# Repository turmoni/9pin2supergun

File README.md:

# 9pin2supergun
A project to read a CD32, Mega Drive/Genesis, or generic 9-pin gamepad and output each control to a separate pin for use with Neo Geos and/or Superguns.

I am personally using this code with a [Monster Joysticks CD32 joystick](https://monsterjoysticks.com/deluxe-cd32-retro-joystick-kit-classic) and a [Minigun Supergun](https://www.arcade-projects.com/threads/minigun-supergun-an-open-source-supergun.9408/).

There is a chance that there will be USB host support in the future, if using [the PCB](pcb/).

## Hardware

There are two expected paths to getting the hardware needed to use this; either build the PCB, or hook up a Pi Pico. For the most compact setup, but needing some more moderate to advanced soldering skills, build the PCB. For a potentially easier build, hook up a Pi Pico.

The PCB's files and some basic instructions can be found in [the pcb directory](pcb/). This isn't for people who are new to soldering - it has surface mount components, a dense layout, and the RP2040 package is very fine pitched.

Schematics and a reference PCB for hooking up a Pi Pico, along with details about the parts used, can be found in [the pico_reference directory](pico_reference/).

## Installation

If you don't want to customise anything, grab the latest uf2 file from [the releases page](https://github.com/turmoni/9pin2supergun/releases/) that matches your setup and install it to your board by holding down BOOTSEL when plugging it in to a PC, and then copying the file on to the storage device that appears. The PCB's BOOTSEL button is at the top-right. The options are:

* 9pin2supergun-**pcb**-v\*.uf2 - if you're using [the PCB I designed](pcb/)
* 9pin2supergun-**pico**-v\*.uf2 - if you're wiring up a Pico as per the schematic

Don't worry if you're missing optional components, the code shouldn't care.

## Usage

Once you've got a board programmed, using it is pretty much a case of setting the switch to the right position, plugging it in, and going! If you've fitted the LED, it will tell you which mode you're in:
* Red: Amiga CD32 mode
* Blue: Mega Drive/generic mode
* Yellow: Mega Drive/generic mode with the buttons swapped

The button mapping is as follows:

| Output | CD32[^1]  | Mega Drive/Genesis (6- or 3-button) | Generic 9-pin |
| ------ | --------  | ----------------------------------- | ------------- |
| Up     | Up        | Up                                  | Up            |
| Down   | Down      | Down                                | Down          |
| Left   | Left      | Left                                | Left          |
| Right  | Right     | Right                               | Right         |
| 1      | G         | A                                   | 1             |
| 2      | Y         | B                                   | 2             |
| 3      | LS        | C                                   | N/A           |
| 4      | R         | X                                   | N/A           |
| 5      | B         | Y                                   | N/A           |
| 6      | RS        | Z                                   | N/A           |
| Start  | Pause     | Start                               | 1 + 2         |
| Coin   | Pause + G | Mode                                | N/A           |

Of course, X, Y, Z, and Mode aren't present on a 3-button Mega Drive controller, so these buttons aren't available there.

Since the Mega Drive layout may be the opposite of what's wanted, you can press and hold mode for three seconds to swap ABC and XYZ.

If you don't want the 1+2 mapping for generic 9-pin controllers, set `MAP_GENERIC_AB_TO_START` to false and rebuild the code. If you don't want the Pause + Green mapping for CD32 controllers, or want it to be a different button combination, change `CD32_COIN_BITMASK` (there are comments in the code to explain its format). Since these are pretty niche, I'm not sure figuring out a runtime configuration option is worth it.

## Building the code

This project is based on the [rp2040 project template](https://github.com/rp-rs/rp2040-project-template), have a look there for details. You need a `rust` build environment and the project will build with Cargo.

If you're using a Pi Pico, rather than the PCB, pass the `--features pi_pico` flag to `cargo` when building to get the right pin assignments.

## Anything else

This polls at 125Hz for the CD32 - I don't know whether a real CD32 pad will be happy with this, but I don't see why it wouldn't. The timing for each polling burst is based on what I observed with my PAL Amiga 500+, so that should be fine, but it was only polling at 50Hz. Given how little time is spent polling compared to waiting even at 125Hz, though, I can't imagine what issues might arise.

The Mega Drive controller support polls at around 140Hz.

Current draw seems fairly low, hovering at around 20-25mA on the controllers I've tested it with. If you're worried, power it up via USB (not whilst connected to a 15-pin port!) and use a USB power meter to see how much it's drawing.

## Credits

Thanks to [Mathew Carr's PSCD32 Development Diary](https://www.mrdictionary.net/PSCD32/diary/2019_08_09.htm) for documenting how the CD32 protocol actually works, and to [the RetroSix Wiki's Mega Drive controller page](https://www.retrosix.wiki/controller-interface-sega-mega-drive) for documenting the Mega Drive bits.

[^1]: Single-letter CD32 buttons refer to the colour, LB and RB are the shoulder buttons

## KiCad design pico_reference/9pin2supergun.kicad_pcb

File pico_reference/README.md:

# 9pin2supergun Reference Pico Design

This is a KiCad project for hooking up a Pi Pico to the appropriate hardware to get a fully working setup. As I see it, there are three main purposes for this project:

* To provide the schematic to use if wiring one up by hand, e.g. on a breadboard
* To give me PCBs based on the schematic so I can test that the schematic I've provided actually works, and is what the code expects
* To give a foundation for making new PCBs with different hardware than what I happened to have on hand

# Using the schematic

The schematic is hopefully fairly simple to understand, and can be found either by opening this project up in KiCad, or by looking at [the rendered PDF](rendered/sch.pdf).

# Building a PCB

First up: you probably don't want to use the PCB I've designed. The layout was literally done in about 20 minutes, with very little care given to routing traces to be neat, and it's designed to use the hardware I had on hand. If you want to use the components I've specified, I recommend instead using [the main PCB](../pcb), which is more compact and not *that* much harder to solder than what I have here.

If you do want to modify it, the KiCad project is in this directory.

For convenience each push gets rendered to [the `rendered` directory](rendered/) as a PDF of the schematics, a set of gerber files, and a BOM as a CSV, but again, you probably don't want to use the generated fabrication files as-is.

# Components and their explanations

If you're going to use your own components, the key things are:
 * U2 ([SN74LVC8T245](https://www.ti.com/product/SN74LVC8T245)) - this is just level shifting the input from the controller down to 3.3V. If you want to try out the Pico's 5V tolerance, you can omit this and RN1 if you want. Often the inputs will be either floating or GND, and so safe anyway, but I wouldn't totally rely on this being the case
 * U3/U4 ([SN74LVC2T45DCUR](https://www.ti.com/product/SN74LVC2T45)) - two-bit level shifters. U3 handles those that are always outputs, and U4 handles pin 6, which can either be an input or an output.
 * RN1 (10k resistor network) - pulling up the inputs from the controller port. Omit it if you're also omitting the level shifters
 * SW1 (SPDT switch) - the mode switch. Switches between Mega Drive (floating) and CD32 (tied to GND) modes. You can hardcode this if you're only using one type of controller
 * SW2 (standard push button) - not actually used, but might be helpful in the future
 * D1 (WS2812B LED) - indicates what mode you're in (including if the button rows are flipped in Mega Drive mode). Omit this if you don't care.

## More on level shifting

To recap, the level shifter U2 handles those inputs that are only ever inputs (pulled up to 5V). U3 handles both of the two outputs that can also be the +5V supply. U4 handles the one remaining pin that's either an input or an output depending on whether it's in CD32 or Mega Drive mode. There is nothing particularly special about any of these, they're just directional level shifters that can handle translating 3.3V to 5V or vice versa.
 
The connections to the DE9 connector are as follows:

| Pin | CD32 Function | CD32 Direction | Mega Drive Function | MD Direction |
| --- | ------------- | -------------- | ------------------- | ------------ |
| 1   | Up            | In             | Up/Z                | In           |
| 2   | Down          | In             | Down/Y              | In           |
| 3   | Left          | In             | Left/X/GND          | In           |
| 4   | Right         | In             | Right/Mode/GND      | In           |
| 5   | Latch         | Out            | +5V                 | Out          |
| 6   | Fire 1/Clock  | Out            | B/A                 | In           |
| 7   | +5V           | Out            | Select              | Out          |
| 8   | GND           | N/A            | GND                 | N/A          |
| 9   | Fire 2/Data   | In             | C/Start             | In           |

As the table shows, the DE9 connector is a lot simpler if you're only targetting a single platform; for a CD32, you can permanently wire pin 7 to +5V, and pin 6 as an output, whereas with a Mega Drive controller you can wire pin 5 to +5V and pin 6 as an input. You may also be able to get away with not needing level shifters in this case, if you're willing to risk +5V into your Pico's GPIO pins, and your controller recognises 3.3V logic levels.

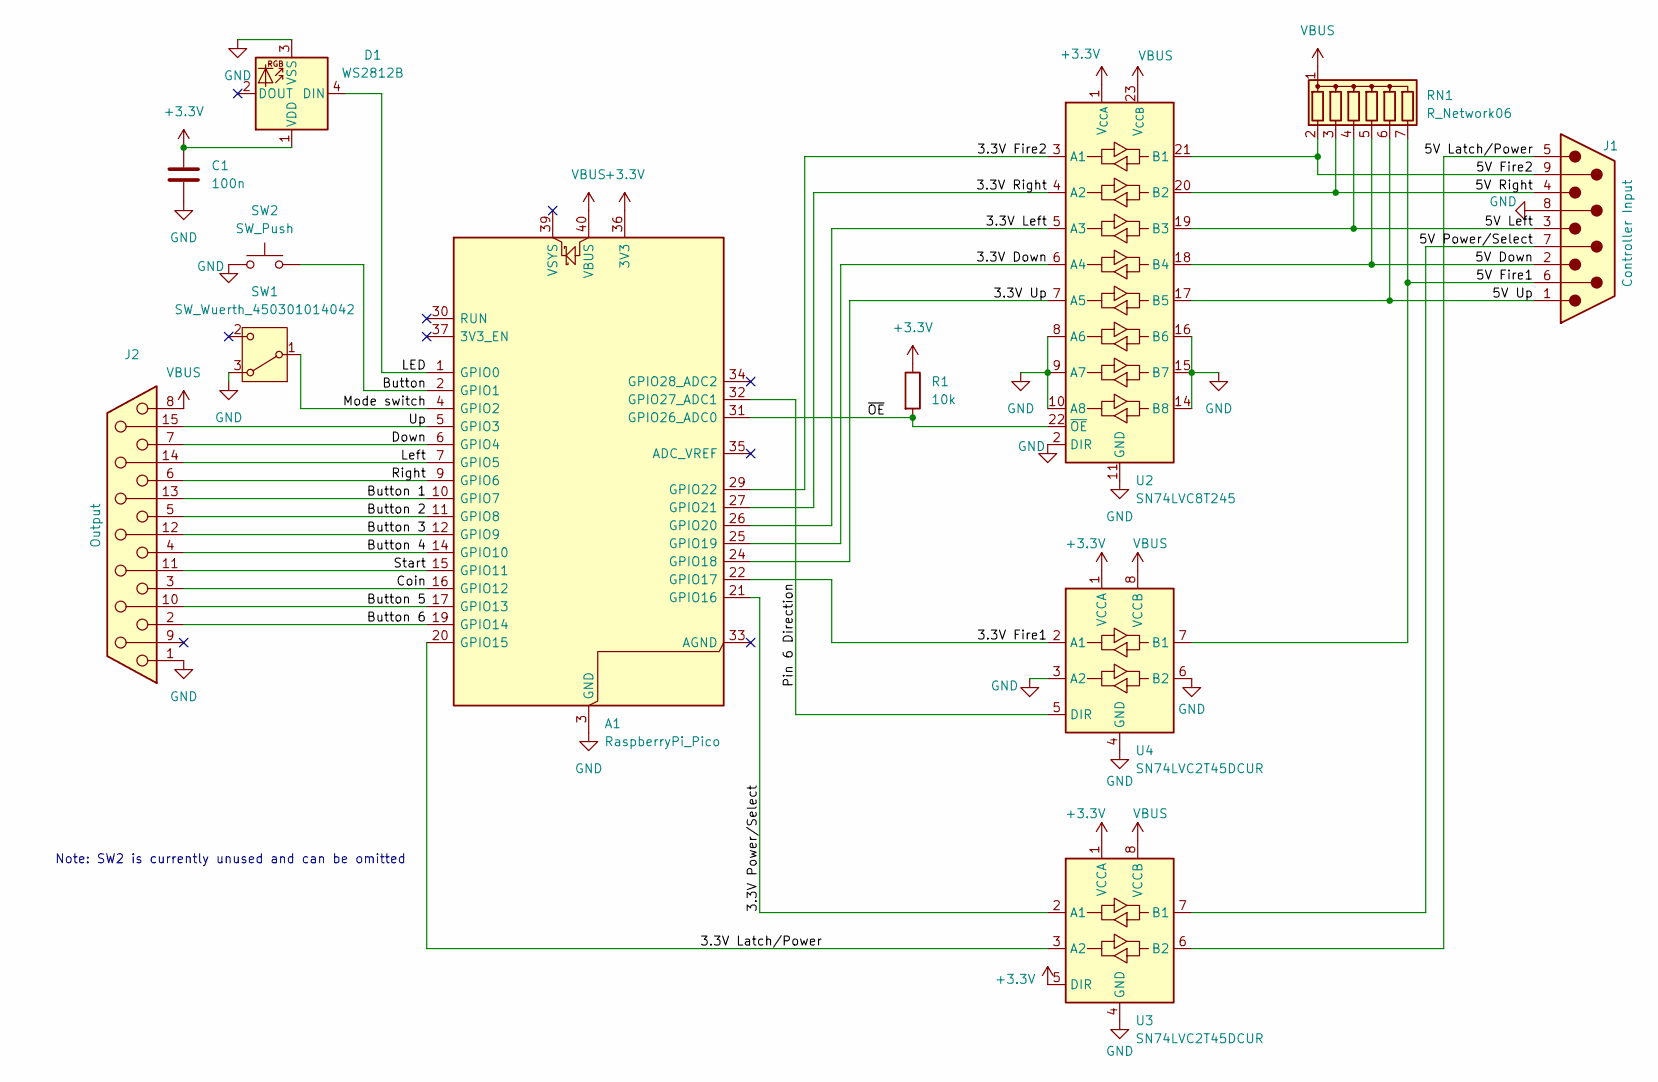
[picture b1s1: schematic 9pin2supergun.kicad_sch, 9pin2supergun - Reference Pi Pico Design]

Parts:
A1: RaspberryPi_Pico; RaspberryPi_Pico_Common_Unspecified
C1: 100n; C_Disc_D5.0mm_W2.5mm_P5.00mm
D1: WS2812B; LED_WS2812B_PLCC4_5.0x5.0mm_P3.2mm
J1: Controller Input; DSUB-9_Pins_Horizontal_P2.77x2.84mm_EdgePinOffset7.70mm_Hou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
J2: Output; DSUB-15_Socket_Horizontal_P2.77x2.84mm_EdgePinOffset7.70mm_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
R1: 10k; R_Axial_DIN0309_L9.0mm_D3.2mm_P12.70mm_Horizontal
RN1: R_Network06; R_Array_SIP7
SW1: SW_Wuerth_450301014042; SW_Slide-03_Wuerth-WS-SLTV_10x2.5x6.4_P2.54mm
SW2: SW_Push; SW_PUSH_6mm
U2: SN74LVC8T245; TSSOP-24_4.4x7.8mm_P0.65mm
U3, U4: SN74LVC2T45DCUR; VSSOP-8_2.3x2mm_P0.5mm

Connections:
+3.3V: A1.36 (3V3), C1.1, D1.1 (VDD), R1.1, U2.1 (V_{CCA}), U3.1 (VCCA), U3.5 (DIR), U4.1 (VCCA)
/3.3V Down: A1.25 (GPIO19), U2.6 (A4)
/3.3V Fire1: A1.22 (GPIO17), U4.2 (A1)
/3.3V Fire2: A1.29 (GPIO22), U2.3 (A1)
/3.3V Latch/Power: A1.20 (GPIO15), U3.3 (A2)
/3.3V Left: A1.26 (GPIO20), U2.5 (A3)
/3.3V Power/Select: A1.21 (GPIO16), U3.2 (A1)
/3.3V Right: A1.27 (GPIO21), U2.4 (A2)
/3.3V Up: A1.24 (GPIO18), U2.7 (A5)
/5V Down: J1.2, RN1.5 (R4), U2.18 (B4)
/5V Fire1: J1.6, RN1.7 (R6), U4.7 (B1)
/5V Fire2: J1.9, RN1.2 (R1), U2.21 (B1)
/5V Latch/Power: J1.5, U3.6 (B2)
/5V Left: J1.3, RN1.4 (R3), U2.19 (B3)
/5V Power/Select: J1.7, U3.7 (B1)
/5V Right: J1.4, RN1.3 (R2), U2.20 (B2)
/5V Up: J1.1, RN1.6 (R5), U2.17 (B5)
/Button: A1.2 (GPIO1), SW2.2
/Button 1: A1.10 (GPIO7), J2.13
/Button 2: A1.11 (GPIO8), J2.5
/Button 3: A1.12 (GPIO9), J2.12
/Button 4: A1.14 (GPIO10), J2.4
/Button 5: A1.17 (GPIO13), J2.10
/Button 6: A1.19 (GPIO14), J2.2
/Coin: A1.16 (GPIO12), J2.3
/Down: A1.6 (GPIO4), J2.7
/LED: A1.1 (GPIO0), D1.4 (DIN)
/Left: A1.7 (GPIO5), J2.14
/Mode switch: A1.4 (GPIO2), SW1.1 (B)
/Pin 6 Direction: A1.32 (GPIO27_ADC1), U4.5 (DIR)
/Right: A1.9 (GPIO6), J2.6
/Start: A1.15 (GPIO11), J2.11 (P111)
/Up: A1.5 (GPIO3), J2.15
/~OE: A1.31 (GPIO26_ADC0), R1.2, U2.22 (~OE)
GND: A1.3 (GND), A1.8 (GND), A1.13 (GND), A1.18 (GND), A1.23 (GND), A1.28 (GND), A1.38 (GND), C1.2, D1.3 (VSS), J1.8, J2.1, SW1.3 (A), SW2.1, U2.2 (DIR), U2.8 (A6), U2.9 (A7), U2.10 (A8), U2.11 (GND), U2.12 (GND), U2.13 (GND), U2.14 (B8), U2.15 (B7), U2.16 (B6), U3.4 (GND), U4.3 (A2), U4.4 (GND), U4.6 (B2)
VBUS: A1.40 (VBUS), J2.8, RN1.1 (common), U2.23 (V_{CCB}), U2.24 (V_{CCB}), U3.8 (VCCB), U4.8 (VCCB)

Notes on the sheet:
Note: SW2 is currently unused and can be omitted

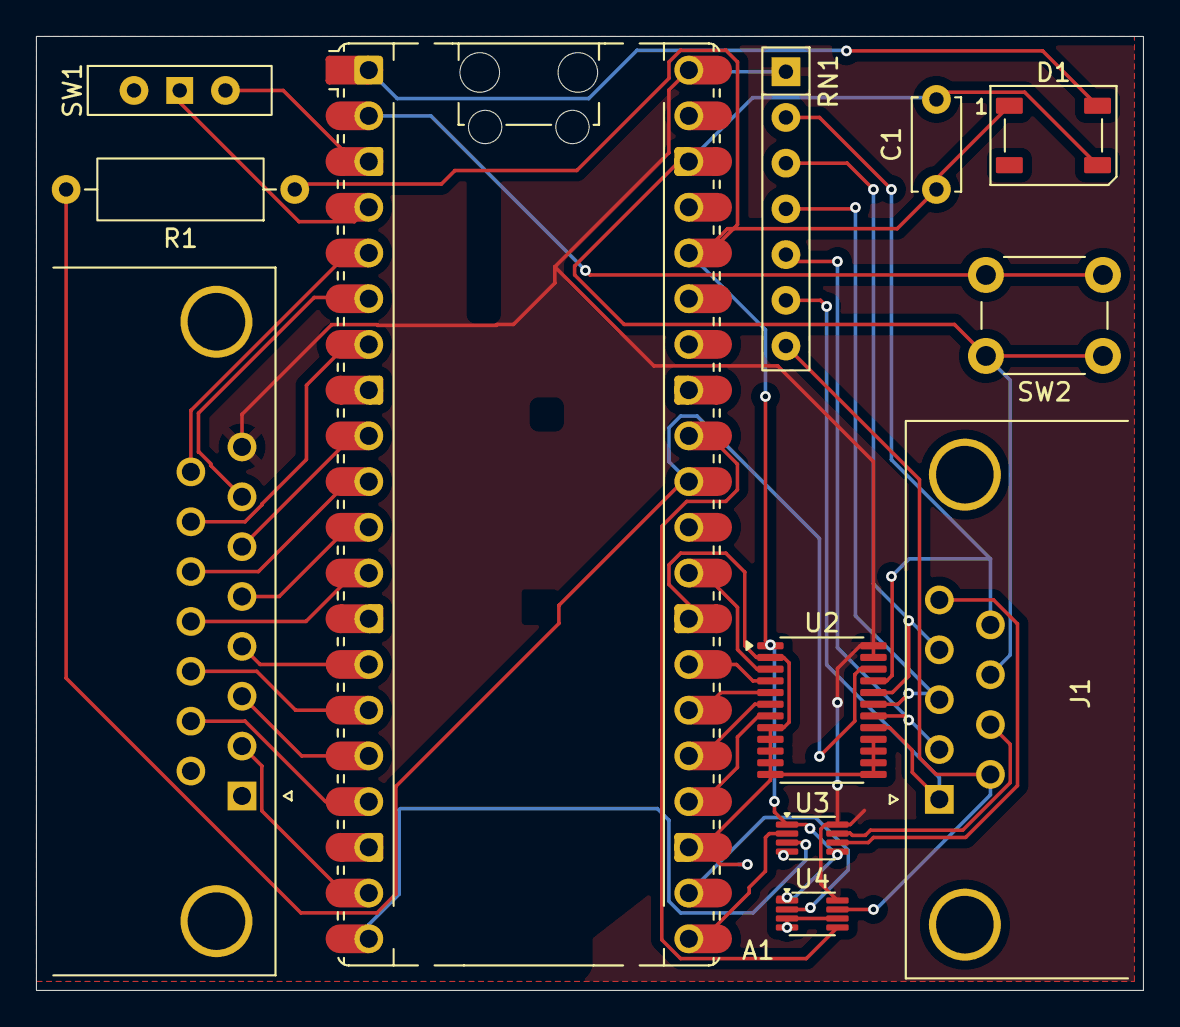
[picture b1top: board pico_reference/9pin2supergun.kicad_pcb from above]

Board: 2 copper layers, 61.5 x 53.0 mm, 12 parts (0 on the bottom side), 36 nets.

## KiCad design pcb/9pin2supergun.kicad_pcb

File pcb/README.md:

# 9pin2supergun PCB

This is a PCB that contains all the components needed for a fully-functional hardware adapter to work with the [9pin2supergun project](/) in a compact package.

## Building one

The KiCad project is in this directory, and for convenience each push gets rendered to [the `rendered` directory](/pcb/rendered/) as a PDF of the schematics, a set of gerber files, and a BOM as a CSV. You *should* be able to use [the gerber archive](/pcb/rendered/gbr.zip) to order boards directly, but for best results you should generate them yourself following your PCB fabricator's instructions (e.g. [for JLCPCB](https://jlcpcb.com/help/article/how-to-generate-gerber-and-drill-files-in-kicad-7)).

Unlike the related [Neo Geo Controller Tester](https://github.com/turmoni/neogeo_controller_tester), this is a moderately advanced soldering job. Don't be scared away from it if you're experienced with soldering (although you may need to learn some new techniques for fine pitched surface-mount components like the RP2040, and you probably want a hot plate, hot air gun, and solder paste), but if you're a complete beginner, this isn't for you.

The [BOM CSV](/pcb/rendered/bom.csv) has the list of parts, but I don't know how useful that is for importing elsewhere. I have [a DigiKey list](https://www.digikey.co.uk/en/mylists/list/U1CG00OTBV) that contains all the components that are needed, although at the time of writing, some of them are not available to order.

You may be able to get this fully/partially assembled from your PCB manufacturer - I didn't do this, so I can't comment, but there are only a few unusual components to manually spec and they are at least in LCSC (JLCPCB)'s database. If I end up doing this, I will probably replace U6 with more of the same type of shifter as U4 and U5 for cost reasons (one less reel to load).

When assembling, note that R2 is marked as DNF - if you're using the specified flash module, you shouldn't need to fit a resistor there. See [Hardware Design with RP2040](https://datasheets.raspberrypi.com/rp2040/hardware-design-with-rp2040.pdf) (PDF) for more information on this, since most of the support circuitry is adapted from that reference design.

## Things to note

SW1 switches between presenting itself as a USB device or a USB host, based on the resistors on the CC pins. This doesn't change anything with the software, and any cables other than Type C to Type C will be entirely unimpacted by this. Set it to Device (up) if you want to plug it into your PC, and Host (down) if you want to plug a gamepad into it. Since there's no code at the moment that uses host mode, it's safe to leave or hardcode it as a device for the moment (connect the middle pins of the switch to their respective top pins, and populate R9 and R10).

Do not power the board from more than one place, e.g. don't plug it into a supergun *and* a USB power source.

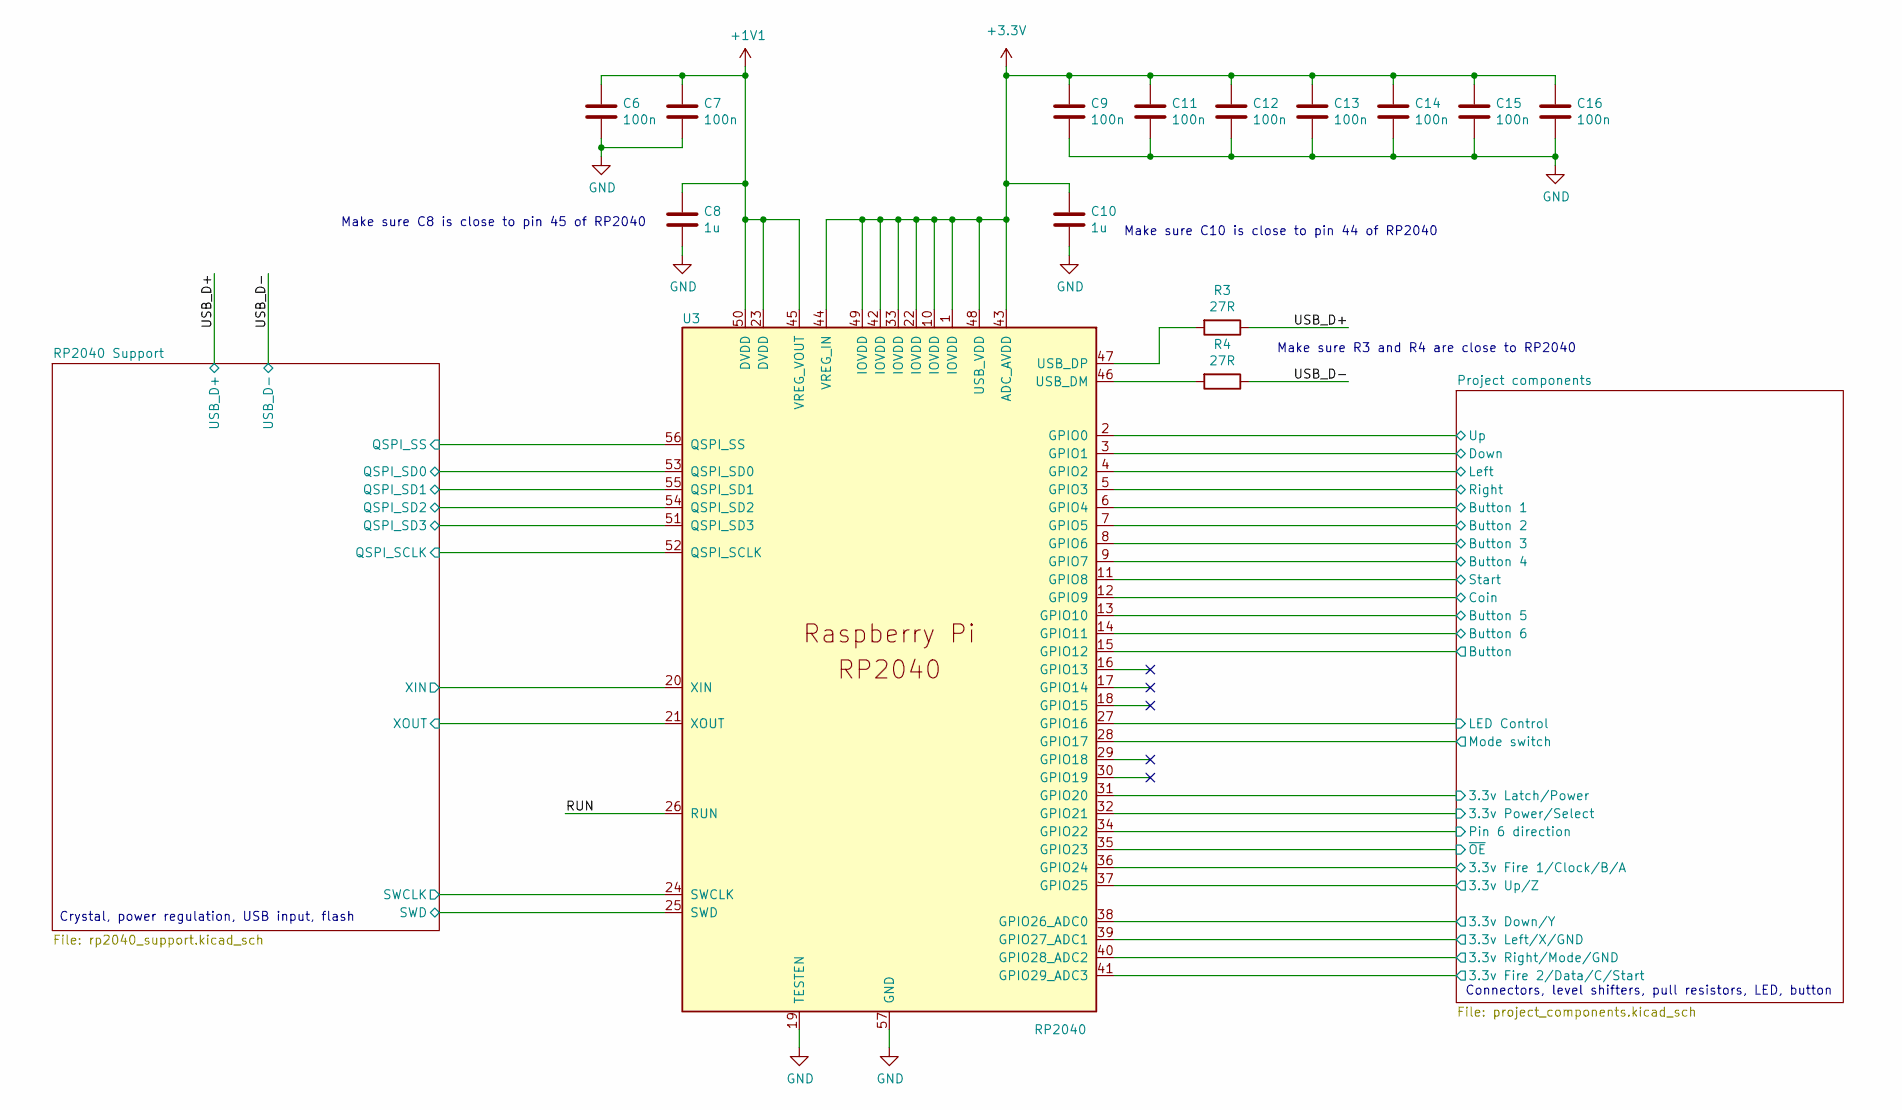
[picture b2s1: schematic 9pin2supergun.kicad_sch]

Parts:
C6, C7, C9, C11, C12, C13, C14, C15, C16: 100n; C_0805_2012Metric_Pad1.18x1.45mm_HandSolder
C8, C10: 1u; C_0805_2012Metric_Pad1.18x1.45mm_HandSolder
R3, R4: 27R; R_0805_2012Metric_Pad1.20x1.40mm_HandSolder
U3: RP2040; RP2040-QFN-56

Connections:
+1V1: C6.1, C7.1, C8.1, U3.23 (DVDD), U3.45 (VREG_VOUT), U3.50 (DVDD)
+3.3V: C9.1, C10.1, C11.1, C12.1, C13.1, C14.1, C15.1, C16.1, U3.1 (IOVDD), U3.10 (IOVDD), U3.22 (IOVDD), U3.33 (IOVDD), U3.42 (IOVDD), U3.43 (ADC_AVDD), U3.44 (VREG_IN), U3.48 (USB_VDD), U3.49 (IOVDD); also elsewhere on the board
/Project components/3.3v Down/Y: U3.38 (GPIO26_ADC0); also elsewhere on the board
/Project components/3.3v Fire 1/Clock/B/A: U3.36 (GPIO24); also elsewhere on the board
/Project components/3.3v Fire 2/Data/C/Start: U3.41 (GPIO29_ADC3); also elsewhere on the board
/Project components/3.3v Latch/Power: U3.31 (GPIO20); also elsewhere on the board
/Project components/3.3v Left/X/GND: U3.39 (GPIO27_ADC1); also elsewhere on the board
/Project components/3.3v Power/Select: U3.32 (GPIO21); also elsewhere on the board
/Project components/3.3v Right/Mode/GND: U3.40 (GPIO28_ADC2); also elsewhere on the board
/Project components/3.3v Up/Z: U3.37 (GPIO25); also elsewhere on the board
/Project components/Button: U3.15 (GPIO12); also elsewhere on the board
/Project components/Button 1: U3.6 (GPIO4); also elsewhere on the board
/Project components/Button 2: U3.7 (GPIO5); also elsewhere on the board
/Project components/Button 3: U3.8 (GPIO6); also elsewhere on the board
/Project components/Button 4: U3.9 (GPIO7); also elsewhere on the board
/Project components/Button 5: U3.13 (GPIO10); also elsewhere on the board
/Project components/Button 6: U3.14 (GPIO11); also elsewhere on the board
/Project components/Coin: U3.12 (GPIO9); also elsewhere on the board
/Project components/Down: U3.3 (GPIO1); also elsewhere on the board
/Project components/LED Control: U3.27 (GPIO16); also elsewhere on the board
/Project components/Left: U3.4 (GPIO2); also elsewhere on the board
/Project components/Mode switch: U3.28 (GPIO17); also elsewhere on the board
/Project components/Pin 6 direction: U3.34 (GPIO22); also elsewhere on the board
/Project components/Right: U3.5 (GPIO3); also elsewhere on the board
/Project components/Start: U3.11 (GPIO8); also elsewhere on the board
/Project components/Up: U3.2 (GPIO0); also elsewhere on the board
/Project components/~OE: U3.35 (GPIO23); also elsewhere on the board
/RP2040 Support/QSPI_SCLK: U3.52 (QSPI_SCLK); also elsewhere on the board
/RP2040 Support/QSPI_SD0: U3.53 (QSPI_SD0); also elsewhere on the board
/RP2040 Support/QSPI_SD1: U3.55 (QSPI_SD1); also elsewhere on the board
/RP2040 Support/QSPI_SD2: U3.54 (QSPI_SD2); also elsewhere on the board
/RP2040 Support/QSPI_SD3: U3.51 (QSPI_SD3); also elsewhere on the board
/RP2040 Support/QSPI_SS: U3.56 (QSPI_SS); also elsewhere on the board
/RP2040 Support/SWCLK: U3.24 (SWCLK); also elsewhere on the board
/RP2040 Support/SWD: U3.25 (SWD); also elsewhere on the board
/RP2040 Support/XIN: U3.20 (XIN); also elsewhere on the board
/RP2040 Support/XOUT: U3.21 (XOUT); also elsewhere on the board
/RUN: U3.26 (RUN)
/USB_D+: R3.1; also elsewhere on the board
/USB_D-: R4.1; also elsewhere on the board
GND: C6.2, C7.2, C8.2, C9.2, C10.2, C11.2, C12.2, C13.2, C14.2, C15.2, C16.2, U3.19 (TESTEN), U3.57 (GND); also elsewhere on the board
unnamed: R4.2, U3.46 (USB_DM)
unnamed: R3.2, U3.47 (USB_DP)

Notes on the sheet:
Crystal, power regulation, USB input, flash
Make sure C8 is close to pin 45 of RP2040
Connectors, level shifters, pull resistors, LED, button
Make sure C10 is close to pin 44 of RP2040
Make sure R3 and R4 are close to RP2040

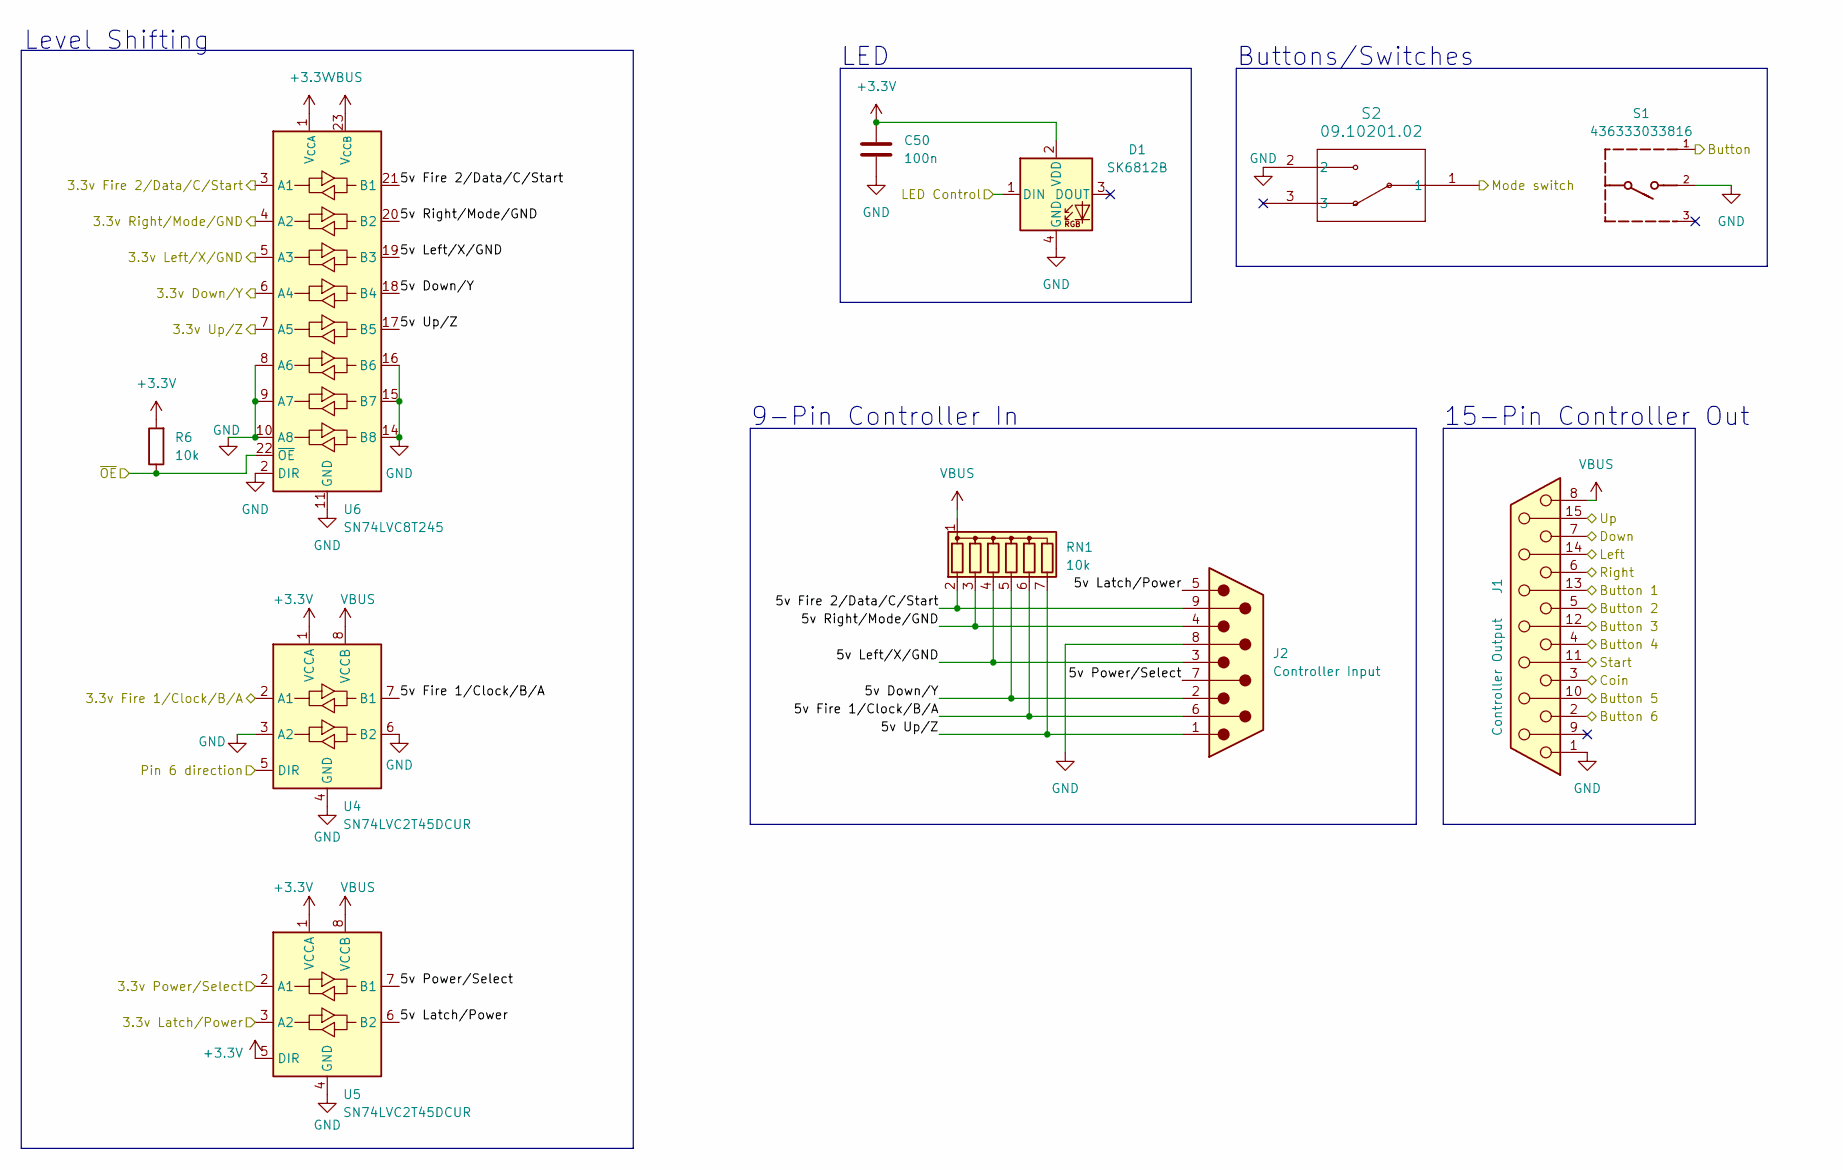
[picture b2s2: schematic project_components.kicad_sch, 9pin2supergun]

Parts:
C50: 100n; C_0805_2012Metric_Pad1.18x1.45mm_HandSolder
D1: SK6812B
J1: Controller Output; DSUB-15_Socket_Horizontal_P2.77x2.84mm_EdgePinOffset7.70mm_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
J2: Controller Input; DSUB-9_Pins_Horizontal_P2.77x2.84mm_EdgePinOffset7.70mm_Hou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
R6: 10k; R_0805_2012Metric_Pad1.20x1.40mm_HandSolder
RN1: 10k; R_Array_SIP7
S1: 436333033816; PART-NUMBER 436333033816
S2: 09.10201.02; SW3_09.10201.02_EAO
U4, U5: SN74LVC2T45DCUR; VSSOP-8_2.3x2mm_P0.5mm
U6: SN74LVC8T245; TSSOP-24_4.4x7.8mm_P0.65mm

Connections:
+3.3V: C50.1, D1.2 (VDD), R6.2, U4.1 (VCCA), U5.1 (VCCA), U5.5 (DIR), U6.1 (V_{CCA}); also elsewhere on the board
/Project components/3.3v Down/Y: U6.6 (A4); also elsewhere on the board
/Project components/3.3v Fire 1/Clock/B/A: U4.2 (A1); also elsewhere on the board
/Project components/3.3v Fire 2/Data/C/Start: U6.3 (A1); also elsewhere on the board
/Project components/3.3v Latch/Power: U5.3 (A2); also elsewhere on the board
/Project components/3.3v Left/X/GND: U6.5 (A3); also elsewhere on the board
/Project components/3.3v Power/Select: U5.2 (A1); also elsewhere on the board
/Project components/3.3v Right/Mode/GND: U6.4 (A2); also elsewhere on the board
/Project components/3.3v Up/Z: U6.7 (A5); also elsewhere on the board
/Project components/5v Down/Y: J2.2 (Down/Y), RN1.5 (R4), U6.18 (B4)
/Project components/5v Fire 1/Clock/B/A: J2.6 (Fire_1/Clock/B/A), RN1.6 (R5), U4.7 (B1)
/Project components/5v Fire 2/Data/C/Start: J2.9 (Fire_2/Data/C/Start), RN1.2 (R1), U6.21 (B1)
/Project components/5v Latch/Power: J2.5 (Latch/+5V), U5.6 (B2)
/Project components/5v Left/X/GND: J2.3 (Left/X/Gnd), RN1.4 (R3), U6.19 (B3)
/Project components/5v Power/Select: J2.7 (+5V/Select), U5.7 (B1)
/Project components/5v Right/Mode/GND: J2.4 (Right/Mode/Gnd), RN1.3 (R2), U6.20 (B2)
/Project components/5v Up/Z: J2.1 (Up/Z), RN1.7 (R6), U6.17 (B5)
/Project components/Button: S1.1; also elsewhere on the board
/Project components/Button 1: J1.13; also elsewhere on the board
/Project components/Button 2: J1.5; also elsewhere on the board
/Project components/Button 3: J1.12; also elsewhere on the board
/Project components/Button 4: J1.4; also elsewhere on the board
/Project components/Button 5: J1.10; also elsewhere on the board
/Project components/Button 6: J1.2; also elsewhere on the board
/Project components/Coin: J1.3; also elsewhere on the board
/Project components/Down: J1.7; also elsewhere on the board
/Project components/LED Control: D1.1 (DIN); also elsewhere on the board
/Project components/Left: J1.14; also elsewhere on the board
/Project components/Mode switch: S2.1; also elsewhere on the board
/Project components/Pin 6 direction: U4.5 (DIR); also elsewhere on the board
/Project components/Right: J1.6; also elsewhere on the board
/Project components/Start: J1.11 (P111); also elsewhere on the board
/Project components/Up: J1.15; also elsewhere on the board
/Project components/~OE: R6.1, U6.22 (~OE); also elsewhere on the board
GND: C50.2, D1.4 (GND), J1.1, J2.8 (GND), S1.2, S2.2, U4.3 (A2), U4.4 (GND), U4.6 (B2), U5.4 (GND), U6.2 (DIR), U6.8 (A6), U6.9 (A7), U6.10 (A8), U6.11 (GND), U6.12 (GND), U6.13 (GND), U6.14 (B8), U6.15 (B7), U6.16 (B6); also elsewhere on the board
VBUS: J1.8, RN1.1 (common), U4.8 (VCCB), U5.8 (VCCB), U6.23 (V_{CCB}), U6.24 (V_{CCB}); also elsewhere on the board

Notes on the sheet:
15-Pin Controller Out
LED
9-Pin Controller In
Buttons/Switches
Level Shifting

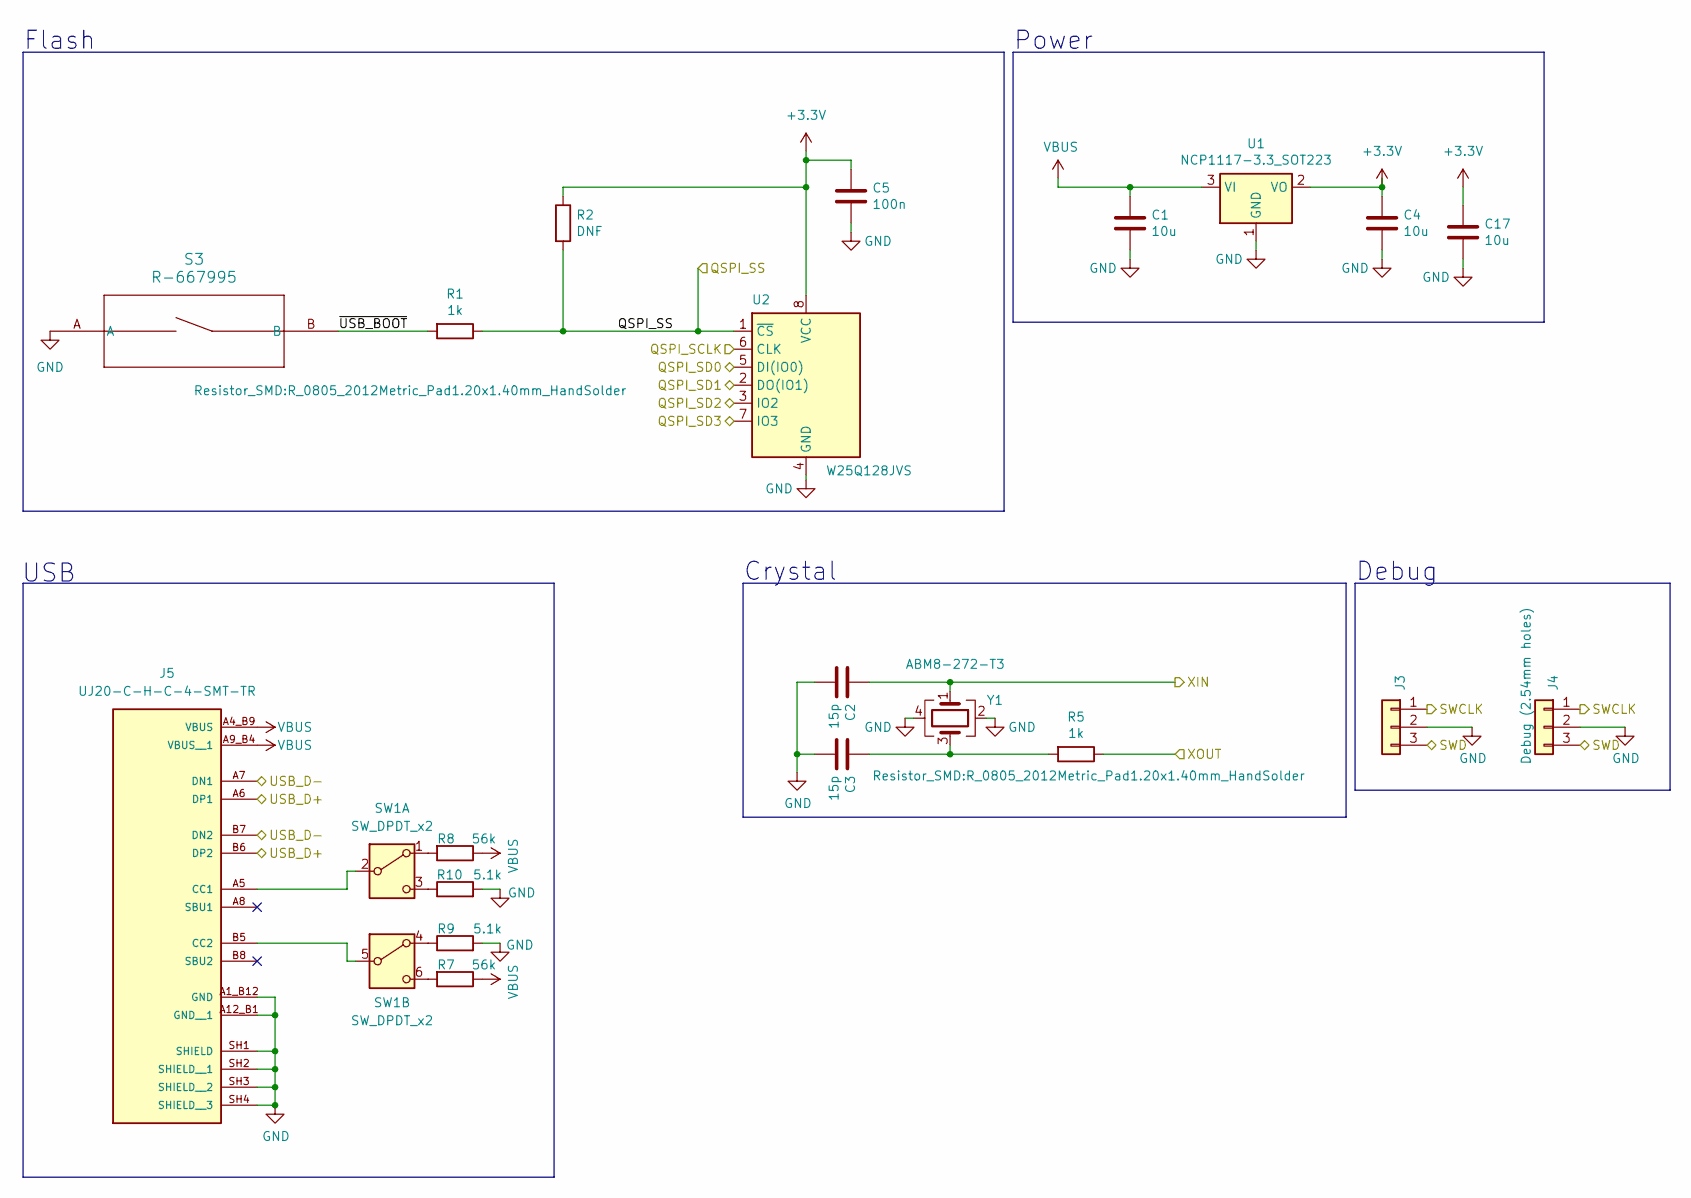
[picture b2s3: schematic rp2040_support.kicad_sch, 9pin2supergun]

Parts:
C1, C4: 10u; C_0805_2012Metric
C2, C3: 15p; C_0805_2012Metric_Pad1.18x1.45mm_HandSolder
C5: 100n; C_0805_2012Metric_Pad1.18x1.45mm_HandSolder
C17: 10u; C_0805_2012Metric_Pad1.18x1.45mm_HandSolder
J3: Debug (JST SH); JST_SH_SM03B-SRSS-TB_1x03-1MP_P1.00mm_Horizontal
J4: Debug (2.54mm holes); PinHeader_1x03_P2.54mm_Vertical
J5: UJ20-C-H-C-4-SMT-TR; CUI_UJ20-C-H-C-4-SMT-TR; PARTREV 1.0
R1, R5: 1k; R_0805_2012Metric_Pad1.20x1.40mm_HandSolder
R2: DNF; R_0402_1005Metric
R7, R8: 56k; R_0805_2012Metric_Pad1.20x1.40mm_HandSolder
R9, R10: 5.1k; R_0805_2012Metric_Pad1.20x1.40mm_HandSolder
S3: R-667995; R-667995_MIT
SW1: SW_DPDT_x2; SW_CK_JS202011CQN_DPDT_Straight
U1: NCP1117-3.3_SOT223; SOT-223-3_TabPin2
U2: W25Q128JVS; SOIC-8_5.23x5.23mm_P1.27mm
Y1: ABM8-272-T3; Crystal_SMD_3225-4Pin_3.2x2.5mm

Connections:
+3.3V: C4.1, C5.1, C17.1, R2.1, U1.2 (VO), U2.8 (VCC); also elsewhere on the board
/RP2040 Support/QSPI_SCLK: U2.6 (CLK); also elsewhere on the board
/RP2040 Support/QSPI_SD0: U2.5 (DI(IO0)); also elsewhere on the board
/RP2040 Support/QSPI_SD1: U2.2 (DO(IO1)); also elsewhere on the board
/RP2040 Support/QSPI_SD2: U2.3 (IO2); also elsewhere on the board
/RP2040 Support/QSPI_SD3: U2.7 (IO3); also elsewhere on the board
/RP2040 Support/QSPI_SS: R1.1, R2.2, U2.1 (~CS); also elsewhere on the board
/RP2040 Support/SWCLK: J3.1, J4.1; also elsewhere on the board
/RP2040 Support/SWD: J3.3, J4.3; also elsewhere on the board
/RP2040 Support/XIN: C2.1, Y1.1; also elsewhere on the board
/RP2040 Support/XOUT: R5.1; also elsewhere on the board
/RP2040 Support/~USB_BOOT: R1.2, S3.B
/USB_D+: J5.A6 (DP1), J5.B6 (DP2); also elsewhere on the board
/USB_D-: J5.A7 (DN1), J5.B7 (DN2); also elsewhere on the board
GND: C1.2, C2.2, C3.2, C4.2, C5.2, C17.2, J3.2, J4.2, J5.A1_B12 (GND), J5.A12_B1 (GND__1), J5.SH1 (SHIELD), J5.SH2 (SHIELD__1), J5.SH3 (SHIELD__2), J5.SH4 (SHIELD__3), R9.2, R10.2, S3.A, U1.1 (GND), U2.4 (GND), Y1.2, Y1.4; also elsewhere on the board
unnamed: C3.1, R5.2, Y1.3
unnamed: J5.A5 (CC1), SW1.2 (B)
unnamed: J5.B5 (CC2), SW1.5 (B)
unnamed: R8.2, SW1.1 (A)
unnamed: R10.1, SW1.3 (C)
unnamed: R9.1, SW1.4 (A)
unnamed: R7.2, SW1.6 (C)
VBUS: C1.1, J5.A4_B9 (VBUS), J5.A9_B4 (VBUS__1), R7.1, R8.1, U1.3 (VI); also elsewhere on the board

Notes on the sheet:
Power
Debug
Crystal
Flash
USB
